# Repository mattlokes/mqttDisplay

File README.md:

# mqttDisplay

## Schematic / BOM
* [BOM](https://htmlpreview.github.io/?https://github.com/mattlokes/mqttDisplay/blob/main/pcb/mqttDisplay/ibom/ibom.html)
* [Schematic](https://github.com/mattlokes/mqttDisplay/blob/main/pcb/mqttDisplay/ibom/mqttDisplay.pdf)

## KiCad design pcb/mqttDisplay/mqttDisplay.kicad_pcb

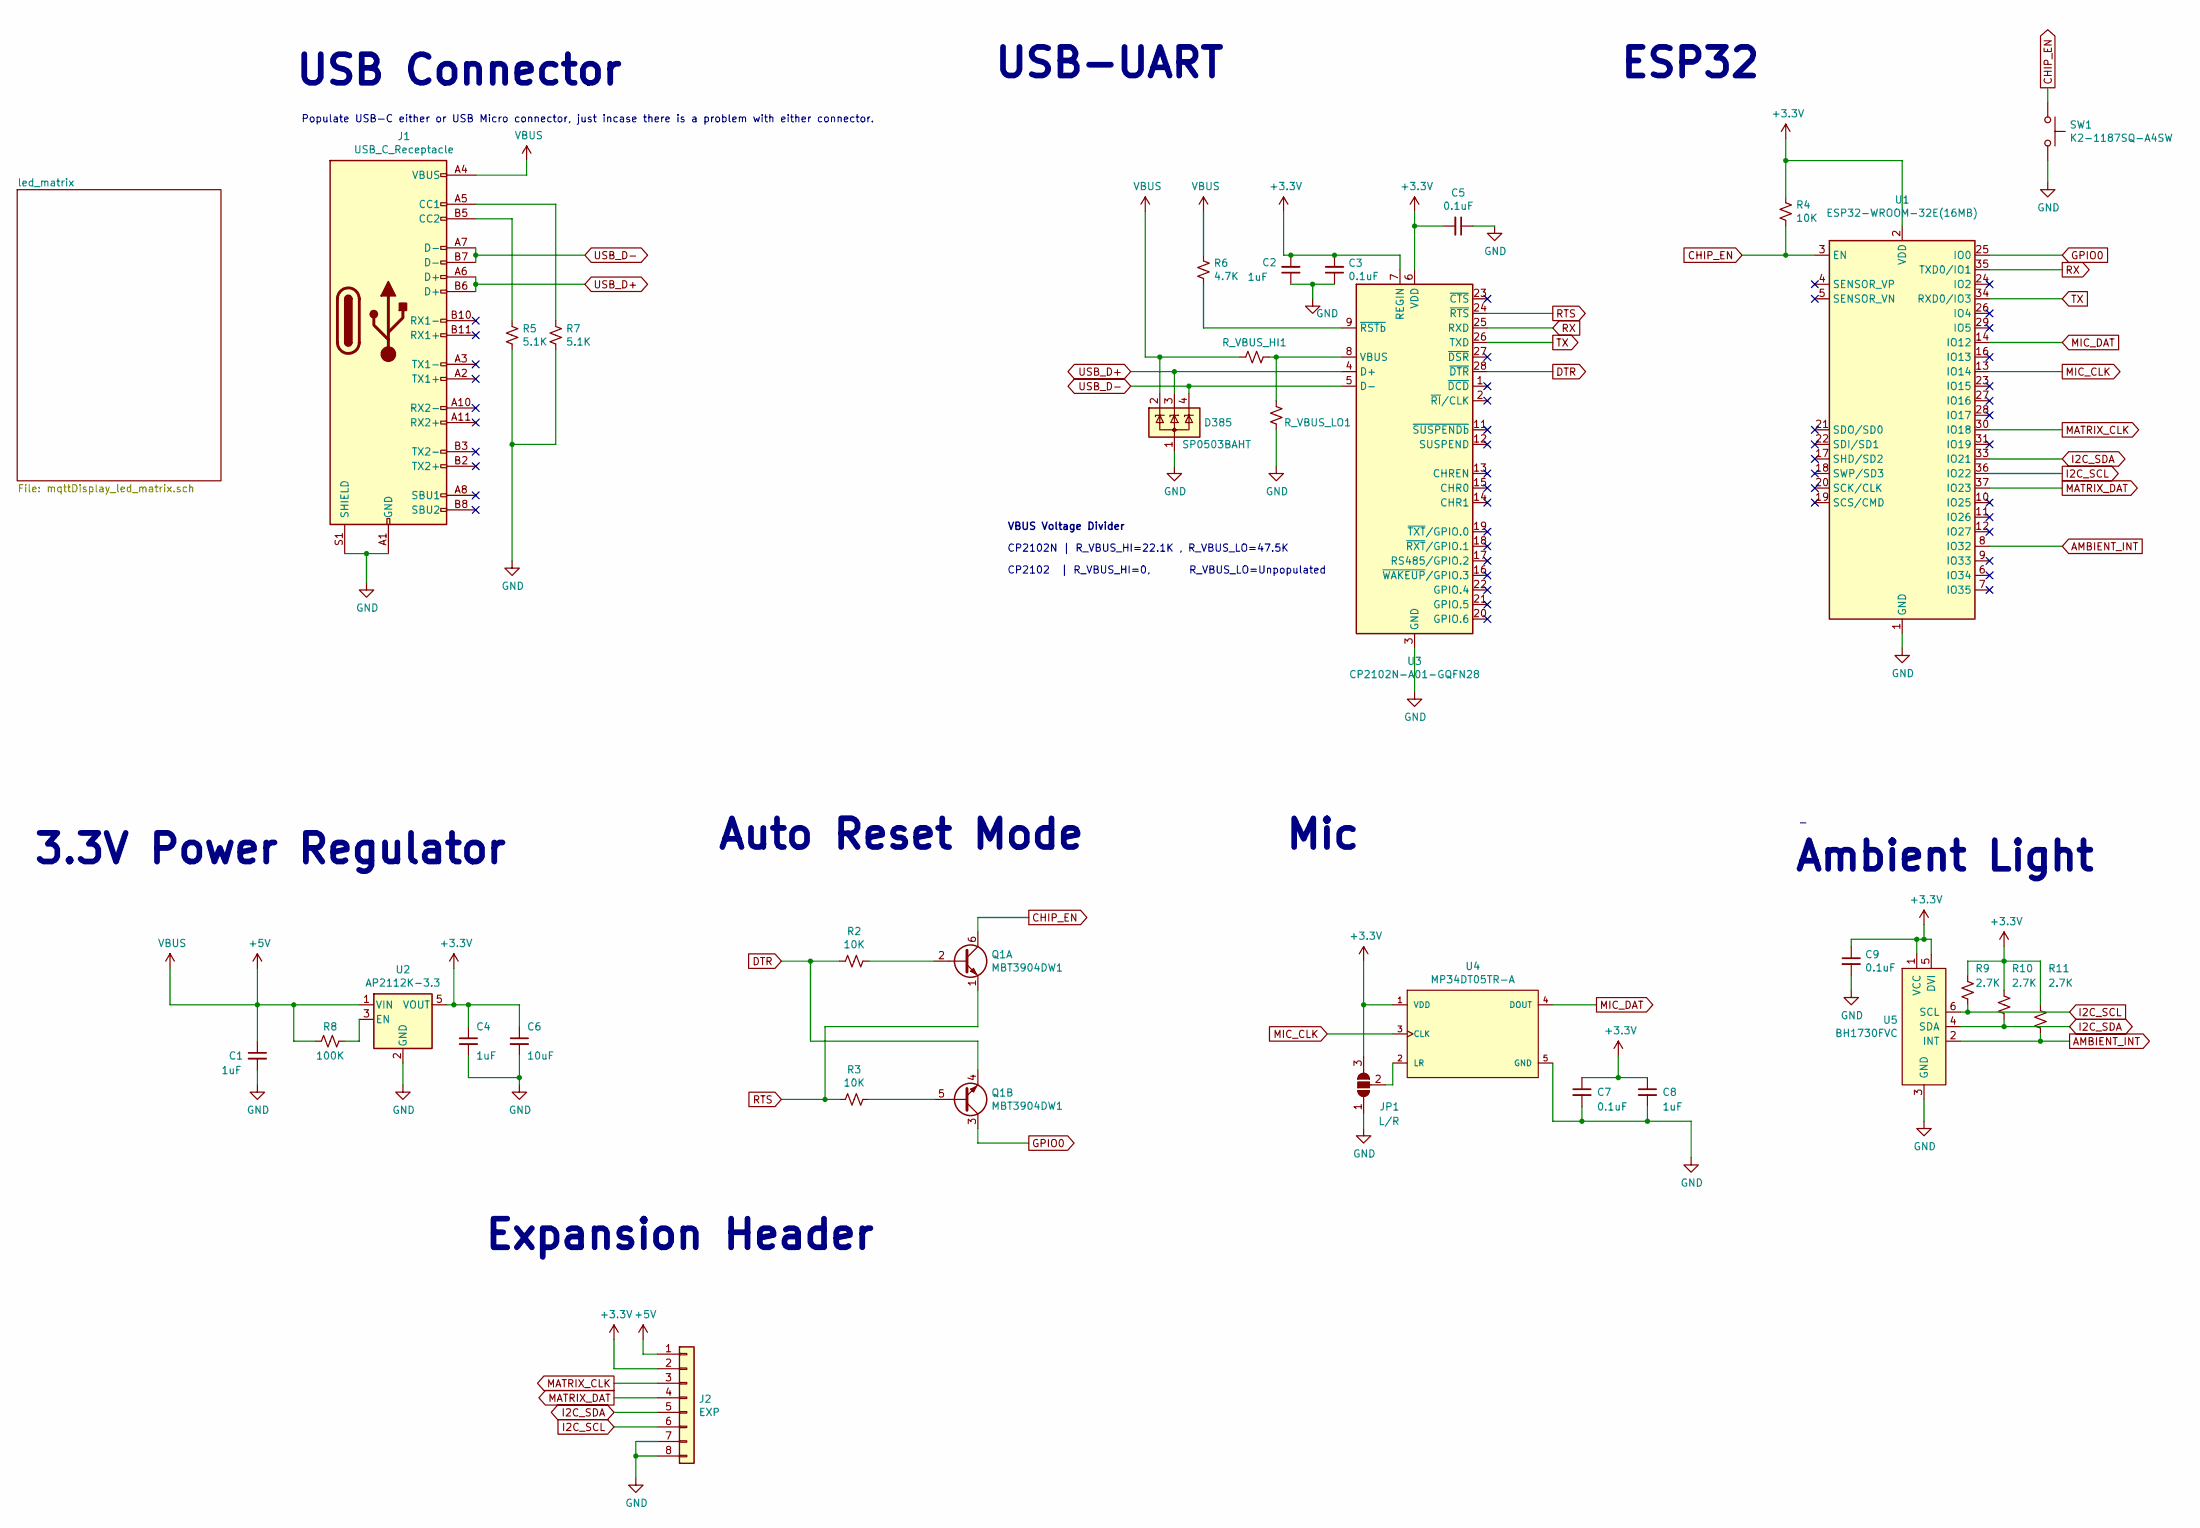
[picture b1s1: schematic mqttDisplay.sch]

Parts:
C1, C2, C4, C8: 1uF; C_0603_1608Metric_Pad1.08x0.95mm_HandSolder; LCSC# C272771
C3, C5, C7, C9: 0.1uF; C_0603_1608Metric_Pad1.08x0.95mm_HandSolder; LCSC# C478888
C6: 10uF; C_0603_1608Metric_Pad1.08x0.95mm_HandSolder; LCSC# C19702
D385: SP0503BAHT; SOT-143; LCSC# C7074
J1: USB_C_Receptacle; USB_C_Receptacle_JING_EXTENSION_C168704_USB2_VERTICAL; LCSC# C168704
J2: EXP; PinHeader_1x08_P2.54mm_Vertical; LCSC# C50981
JP1: L/R; SolderJumper-3_P1.3mm_Open_RoundedPad1.0x1.5mm; LCSC# --
Q1: MBT3904DW1; SOT-363_SC-70-6; LCSC# C110150
R2, R3, R4: 10K; R_0603_1608Metric_Pad0.98x0.95mm_HandSolder; LCSC# C441897
R5, R7: 5.1K; R_0603_1608Metric_Pad0.98x0.95mm_HandSolder; LCSC# C14677
R6: 4.7K; R_0603_1608Metric_Pad0.98x0.95mm_HandSolder; LCSC# C163915
R8: 100K; R_0603_1608Metric_Pad0.98x0.95mm_HandSolder; LCSC# C189597
R9, R10, R11: 2.7K; R_0603_1608Metric_Pad0.98x0.95mm_HandSolder; LCSC# C403121
R_VBUS_HI1: 0; R_0603_1608Metric_Pad0.98x0.95mm_HandSolder; LCSC# C100044
R_VBUS_LO1: 0; R_0603_1608Metric_Pad0.98x0.95mm_HandSolder; LCSC# C100044
SW1: K2-1187SQ-A4SW; SW_SPST_TL3342; LCSC# C92584
U1: ESP32-WROOM-32E(16MB); ESP32-WROOM-32; LCSC# C701343
U2: AP2112K-3.3; SOT-23-5; LCSC# C51118
U3: CP2102N-A01-GQFN28; QFN-28-1EP_5x5mm_P0.5mm_EP3.35x3.35mm; LCSC# C6568
U4: MP34DT05TR-A; STMicroelectronics-HCLGA-DM00231908-0-3-MFG; mouser part number 511-MP34DT05TR-A; digikey description MICROPHONE MEMS DIGITAL PDM OMNI
U5: BH1730FVC; WSOF6; LCSC# C79616

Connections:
+3V3: C2.2, C3.2, C4.1, C5.2, C6.1, C7.1, C8.1, C9.1, J2.2, JP1.3 (B), R4.1, R9.1, R10.1, R11.1, U1.2 (VDD), U2.5 (VOUT), U3.6 (VDD), U3.7 (REGIN), U4.1 (VDD), U5.1 (VCC), U5.5 (DVI)
+5V: C1.1, D385.2 (K), J1.A4 (VBUS), J1.A9 (VBUS), J1.B4 (VBUS), J1.B9 (VBUS), J2.1, R6.1, R8.2, R_VBUS_HI1.2, U2.1 (VIN); also elsewhere on the board
AMBIENT_INT: R11.2, U1.8 (IO32), U5.2 (INT)
CHIP_EN: Q1.6 (C1), R4.2, SW1.1, U1.3 (EN)
DTR: Q1.4 (E2), R2.2, U3.28 (~DTR)
GND: C1.2, C2.1, C3.1, C4.2, C5.1, C6.2, C7.2, C8.2, C9.2, D385.1 (A), J1.A1 (GND), J1.A12 (GND), J1.B1 (GND), J1.B12 (GND), J1.S1 (SHIELD), J1.SHIELD, J2.7, J2.8, JP1.1 (A), R5.1, R7.1, R_VBUS_LO1.2, SW1.2, U1.1 (GND), U1.15 (GND), U1.38 (GND), U1.39 (GND), U2.2 (GND), U3.3 (GND), U3.29 (GND), U4.5 (GND), U5.3 (GND); also elsewhere on the board
GPIO0: Q1.3 (C2), U1.25 (IO0)
I2C_SCL: J2.6, R9.2, U1.36 (IO22), U5.6 (SCL)
I2C_SDA: J2.5, R10.2, U1.33 (IO21), U5.4 (SDA)
MATRIX_CLK: J2.3, U1.30 (IO18); also elsewhere on the board
MATRIX_DAT: J2.4, U1.37 (IO23); also elsewhere on the board
MIC_CLK: U1.13 (IO14), U4.3 (CLK)
MIC_DAT: U1.14 (IO12), U4.4 (DOUT)
unnamed: J1.A5 (CC1), R7.2
unnamed: J1.B5 (CC2), R5.2
unnamed: JP1.2 (C), U4.2 (LR)
unnamed: Q1.2 (B1), R2.1
unnamed: Q1.5 (B2), R3.1
unnamed: R6.2, U3.9 (~RSTb)
unnamed: R8.1, U2.3 (EN)
unnamed: R_VBUS_HI1.1, R_VBUS_LO1.1, U3.8 (VBUS)
RTS: Q1.1 (E1), R3.2, U3.24 (~RTS)
RX: U1.35 (TXD0/IO1), U3.25 (RXD)
TX: U1.34 (RXD0/IO3), U3.26 (TXD)
USB_D+: D385.3 (K), J1.A6 (D+), J1.B6 (D+), U3.4 (D+)
USB_D-: D385.4 (K), J1.A7 (D-), J1.B7 (D-), U3.5 (D-)

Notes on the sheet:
Expansion Header
Ambient Light
Mic
ESP32
Auto Reset Mode
CP2102 | R_VBUS_HI=0, R_VBUS_LO=Unpopulated
CP2102N | R_VBUS_HI=22.1K , R_VBUS_LO=47.5K
VBUS Voltage Divider
USB-UART
USB Connector
Populate USB-C either or USB Micro connector, just incase there is a problem with either connector.
3.3V Power Regulator
